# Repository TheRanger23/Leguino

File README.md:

# Leguino
Lego 9767 card with connection to Arduino Nano, not yet tested or code written

Bill Of Materials:

C1: 10uF
C2: 100nF
C3: 100nF
T1: BC557B
R1: 2.2K Ohm

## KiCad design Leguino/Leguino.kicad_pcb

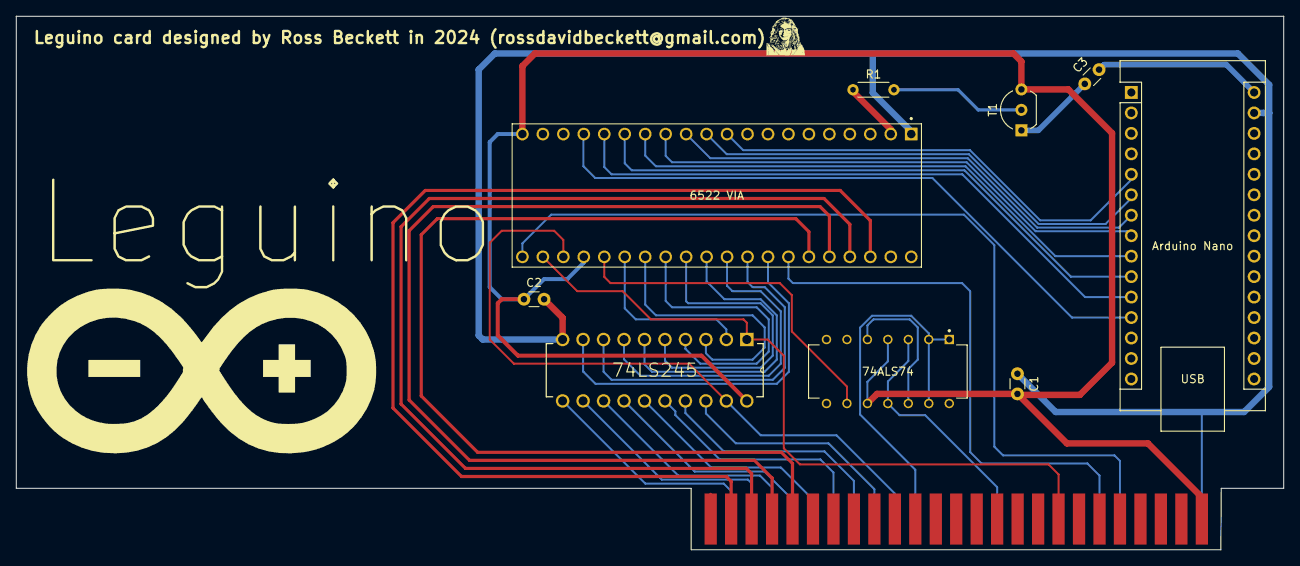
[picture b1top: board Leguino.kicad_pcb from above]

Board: 2 copper layers, 157.3 x 66.2 mm, 10 parts (0 on the bottom side), 29 nets.

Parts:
74ALS74: DIP794W45P254L1969H508Q14
74LS245: DIP254P762X508-20
6522 VIA: AMPHENOL_DILB40P-223TLF
Arduino Nano: Arduino_Nano
C1, C2, C3: C1; C_Disc_D3.0mm_W1.6mm_P2.50mm
J1: CARD EDGE; AppleIIBus
R1: R_Axial_DIN0204_L3.6mm_D1.6mm_P5.08mm_Horizontal
T1: TO-92_Inline_Wide_CEB

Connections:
+5V: 74ALS74.10, 74LS245.20, 6522 VIA.+5V, 6522 VIA.CS1, C1.2, C2.1, C3.1, J1.25, T1.1, T1.3
/7M: 74ALS74.3, 74ALS74.11, J1.36
/A0: 6522 VIA.38, J1.2
/A1: 6522 VIA.37, J1.3
/A2: 6522 VIA.36, J1.4
/A3: 6522 VIA.35, J1.5
/D0: 74LS245.11, J1.49
/D1: 74LS245.12, J1.48
/D2: 74LS245.13, J1.47
/D3: 74LS245.14, J1.46
/D4: 74LS245.15, J1.45
/D5: 74LS245.16, J1.44
/D6: 74LS245.17, J1.43
/D7: 74LS245.18, J1.42
/PHI0: 74ALS74.2, J1.40
/R~W: 74LS245.1, 6522 VIA.22, J1.18
/~DEVSEL: 74LS245.19, 6522 VIA.23, J1.41
/~IRQ: 6522 VIA.21, J1.30
/~RES: 6522 VIA.34, J1.31
GND: 74LS245.10, 6522 VIA.VSS, Arduino Nano.29, C1.1, C2.2, J1.26
PA0: 6522 VIA.PA0, R1.1, R1.2, T1.2
PB0: 6522 VIA.PB0, Arduino Nano.5
PB1: 6522 VIA.PB1, Arduino Nano.6
PB2: 6522 VIA.PB2, Arduino Nano.7
PB3: 6522 VIA.PB3, Arduino Nano.8
PB4: 6522 VIA.PB4, Arduino Nano.9
PB5: 6522 VIA.PB5, Arduino Nano.10
PB6: 6522 VIA.PB6, Arduino Nano.11
PB7: 6522 VIA.PB7, Arduino Nano.12
